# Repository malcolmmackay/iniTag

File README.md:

# pHAT Passive Tag 

Coming soon.

## Licence

### Software

### Hardware

[CERN Open Hardware Licence Version 2 - Strongly Reciprocal](https://ohwr.org/cern_ohl_s_v2.txt)

### Documentation

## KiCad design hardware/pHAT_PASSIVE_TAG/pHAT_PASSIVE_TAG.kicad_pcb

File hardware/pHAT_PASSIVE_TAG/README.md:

# RFM69HCW-868-S2 Partial HAT for pi Zero
This project includes KiCAD 5.0 CAD files to make a pi Zero HAT with connections from SPI0 device 0 to an RFM69HCW-868-S2 868 MHz transceiver. It was inspired by the OpenAPS project: https://github.com/openaps/openaps.

This board makes connections from the table on https://openaps.readthedocs.io/en/latest/docs/Gear%20Up/edison.html#hardware-information-for-pi-based-setups-with-rfm69hcw-experimental 

| Board | Connect | Connect | Connect | Connect | Connect | Connect | Connect | Connect |
| ----- | ------- | ------- | ------- | ------- | ------- | ------- | ------- | ------- |
| RPi | 3.3V | GND | MOSI | MISO | SCLK | | CEO_N | | 
| RPi PIN | 17 | 25 | 19 | 21 | 23 | 16 | 24 | 18 |
| RFM69HCW | VIN or 3.3V | GND | MOSI | MISO | SCK or CLK | G0 or DIO0 | CS or NSS | RST or RESET |

One of five prototypes made by Eurocircuits for £42 was tested successfully with OpenAPS after following instructions to switch to the development branch.

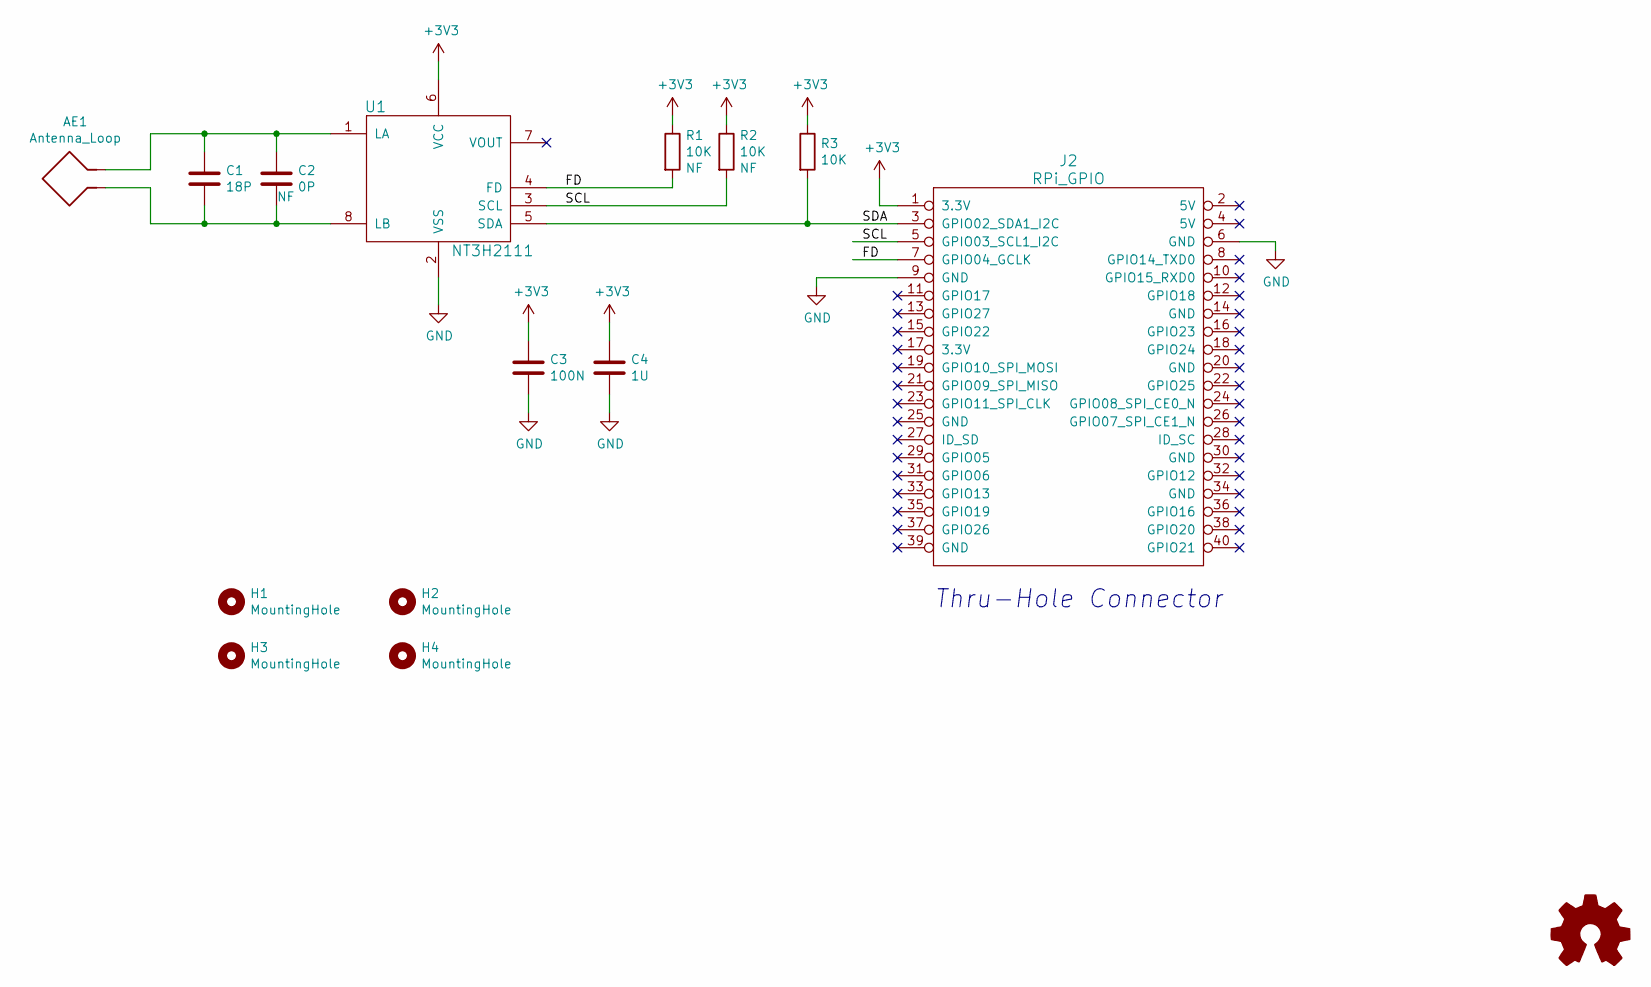
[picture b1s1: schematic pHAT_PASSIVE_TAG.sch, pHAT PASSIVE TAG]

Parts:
AE1: Antenna_Loop; Class_6_NXP_7loop_150u_OUTSIDE
C1: 18P; C_0603
C2: 0P; C_0603
C3: 100N; C_0603
C4: 1U; C_0603
H1, H2, H3, H4: MountingHole; RPi_Hat_Mounting_Hole
J2: RPi_GPIO; PinSocket_2x20_P2.54mm_Vertical
LOGO1: Logo_Open_Hardware_Small; OSHW-Symbol_5.7x6mm_SilkScreen
R1, R2, R3: 10K; R_0603_1608Metric
U1: NT3H2111; SO-8_3.9x4.9mm_P1.27mm

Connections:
+3V3: C3.1, C4.1, J2.1 (3.3V), R1.1, R2.1, R3.1, U1.6 (VCC)
/FD: J2.7 (GPIO04_GCLK), R1.2, U1.4 (FD)
/SCL: J2.5 (GPIO03_SCL1_I2C), R2.2, U1.3 (SCL)
/SDA: J2.3 (GPIO02_SDA1_I2C), R3.2, U1.5 (SDA)
GND: C3.2, C4.2, J2.6 (GND), J2.9 (GND), U1.2 (VSS)
unnamed: AE1.1, C1.1, C2.1, U1.1 (LA)
unnamed: AE1.2, C1.2, C2.2, U1.8 (LB)

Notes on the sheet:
Thru-Hole Connector

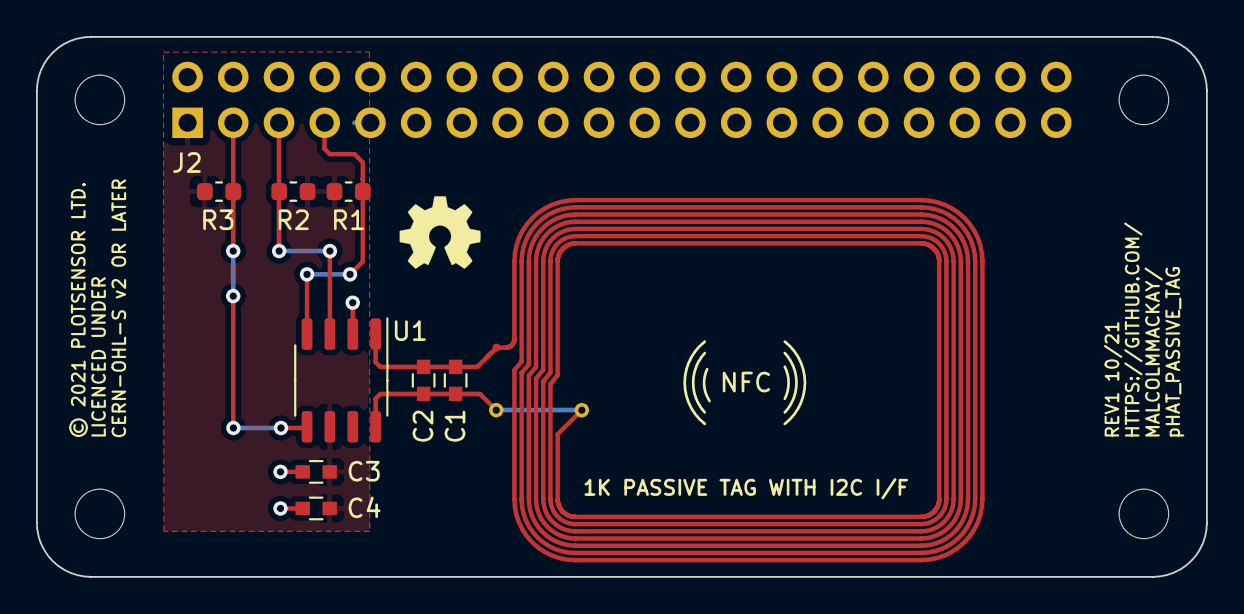
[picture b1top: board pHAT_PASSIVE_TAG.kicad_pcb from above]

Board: 2 copper layers, 65.0 x 30.0 mm, 15 parts (1 on the bottom side), 7 nets.

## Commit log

2021-10-16 Removed firmware and added web application
    There will be no MSP430 on this board.
2021-10-20 Release 1.
2021-10-20 Added pHAT_PASSIVE_TAG
2021-10-26 Added bottom solder mask
2021-11-14 Removed web app. Added script that writes NFC text record.

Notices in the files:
README.md:
License: Apache v2
License: CC BY-SA 4.0
hardware/pHAT_PASSIVE_TAG/pHAT_PASSIVE_TAG.kicad_pcb:
MIT Licensed Open Source Hardware
© 2021 PLOTSENSOR LTD.
LICENCED UNDER
CERN-OHL-S v2 OR LATER
hardware/pHAT_PASSIVE_TAG/pHAT_PASSIVE_TAG.sch:
COPYRIGHT Plotsensor Ltd. 2021
Licenced under CERN OHL-v2-S
